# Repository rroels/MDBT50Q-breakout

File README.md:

# Raytac MDBT50Q (nRF52840) Breakout Board

> [!WARNING]
> The information and material (code, designs, files, ...) are provided "AS IS". We make no representation or warranty of any kind, express or implied, regarding the accuracy, adequacy, validity, reliability, availability, or completeness of any information or material. Use this at your own risk.

## Introduction

This is a breakout board for the Raytac MDBT50Q, which is small module based on the Nordic nRF52840 microcontroller.

[https://www.raytac.com/product/ins.php?index_id=24](https://www.raytac.com/product/ins.php?index_id=24)

This breakout board works with all three variants, since the only difference is their antenna:

* MDBT50Q-1MV2
* MDBT50Q-U1MV2
* MDBT50Q-P1MV2

Note that these modules are sometimes sold by other vendors, who put their own branding on the module:

* [https://www.adafruit.com/product/4078](https://www.adafruit.com/product/4078)
* [https://www.seeedstudio.com/MDBT50Q-1M-nRF52840-Based-BLE-Module-p-3147.html](https://www.seeedstudio.com/MDBT50Q-1M-nRF52840-Based-BLE-Module-p-3147.html)

This breakout board adds some power management and exposes most of the pins:

> [!WARNING]
> GPIO pins marked as "SLOW IO" are not slow per se. However, Nordic does not recommend using them for high frequency signals (e.g. SPI or I2C), as they may cause, or be subject to, interference (they are closest to the radio of the nRF52840).

## Change Log

* v1.0
  * Initial design 

## Design Considerations

* on-board 5V to 3.3V converter
* external 32.768K crystal (optional for the MDBT50Q module)
* ESD diode 
* reset button
* 1 LED 

## Schematics 

> [!WARNING]
> GPIO pins marked as "SLOW IO" are not slow per se. However, Nordic does not recommend using them for high frequency signals (e.g. SPI or I2C), as they may cause, or be subject to, interference (they are closest to the radio of the nRF52840).

## How to Obtain the Physical PCB

The Gerber file is in this repository (`gerber/MDBT50Q-breakout.zip`). Simply upload this file a PCB manufacturer of your choice (JLPCB, PCBWay, ...), and you they will make it for you for as low as \$5 for 5 pieces (with the cheapest shipping option, which can take a few weeks).

For JLCPCB, select the order number option where they will replace "JLCJLCJLCJLC" on the board with the actual order number.

> [!WARNING]
> Note that will still have to solder the components onto the PCB yourself!

## How to Edit Design

Everything you need to edit this design in KiCad 8 is included in the repository.

However, this project uses symbols, footprints and 3D models from [Component Search Engine](https://componentsearchengine.com/). Their license allows us to do pretty much whatever we want with them, except redistributing them. For this reason I can't include them in this repository.

If you would like to edit the design yourself, you will need to download the following component libraries from [https://componentsearchengine.com/](https://componentsearchengine.com/) (it's free!):

* [https://componentsearchengine.com/part-view/TS-1187A-C-D-B/XKB%20Connectivity](https://componentsearchengine.com/part-view/TS-1187A-C-D-B/XKB%20Connectivity)

You also need these from SnapEDA:

* [https://www.snapeda.com/parts/21296912/TE%20Connectivity/view-part/?ref=te_in&t=USB4105-GF-A&con_ref=None](https://www.snapeda.com/parts/21296912/TE%20Connectivity/view-part/?ref=te_in&t=USB4105-GF-A&con_ref=None)

From the downloaded zip files, move the content of the `KiCad` and `3D` subfolders into the project structure, so that the end-result looks like this:

The KiCad project is configured to look for these files in these locations, using relative paths, so no changes to the project itself are required.

## Future Work

* Improve routing
	* use more than 2 layer PCBs
* Add another push button for better compatibility with the Adafruit nRF52 bootloader	

## Sources

* [https://www.raytac.com/product/ins.php?index_id=24](https://www.raytac.com/product/ins.php?index_id=24)

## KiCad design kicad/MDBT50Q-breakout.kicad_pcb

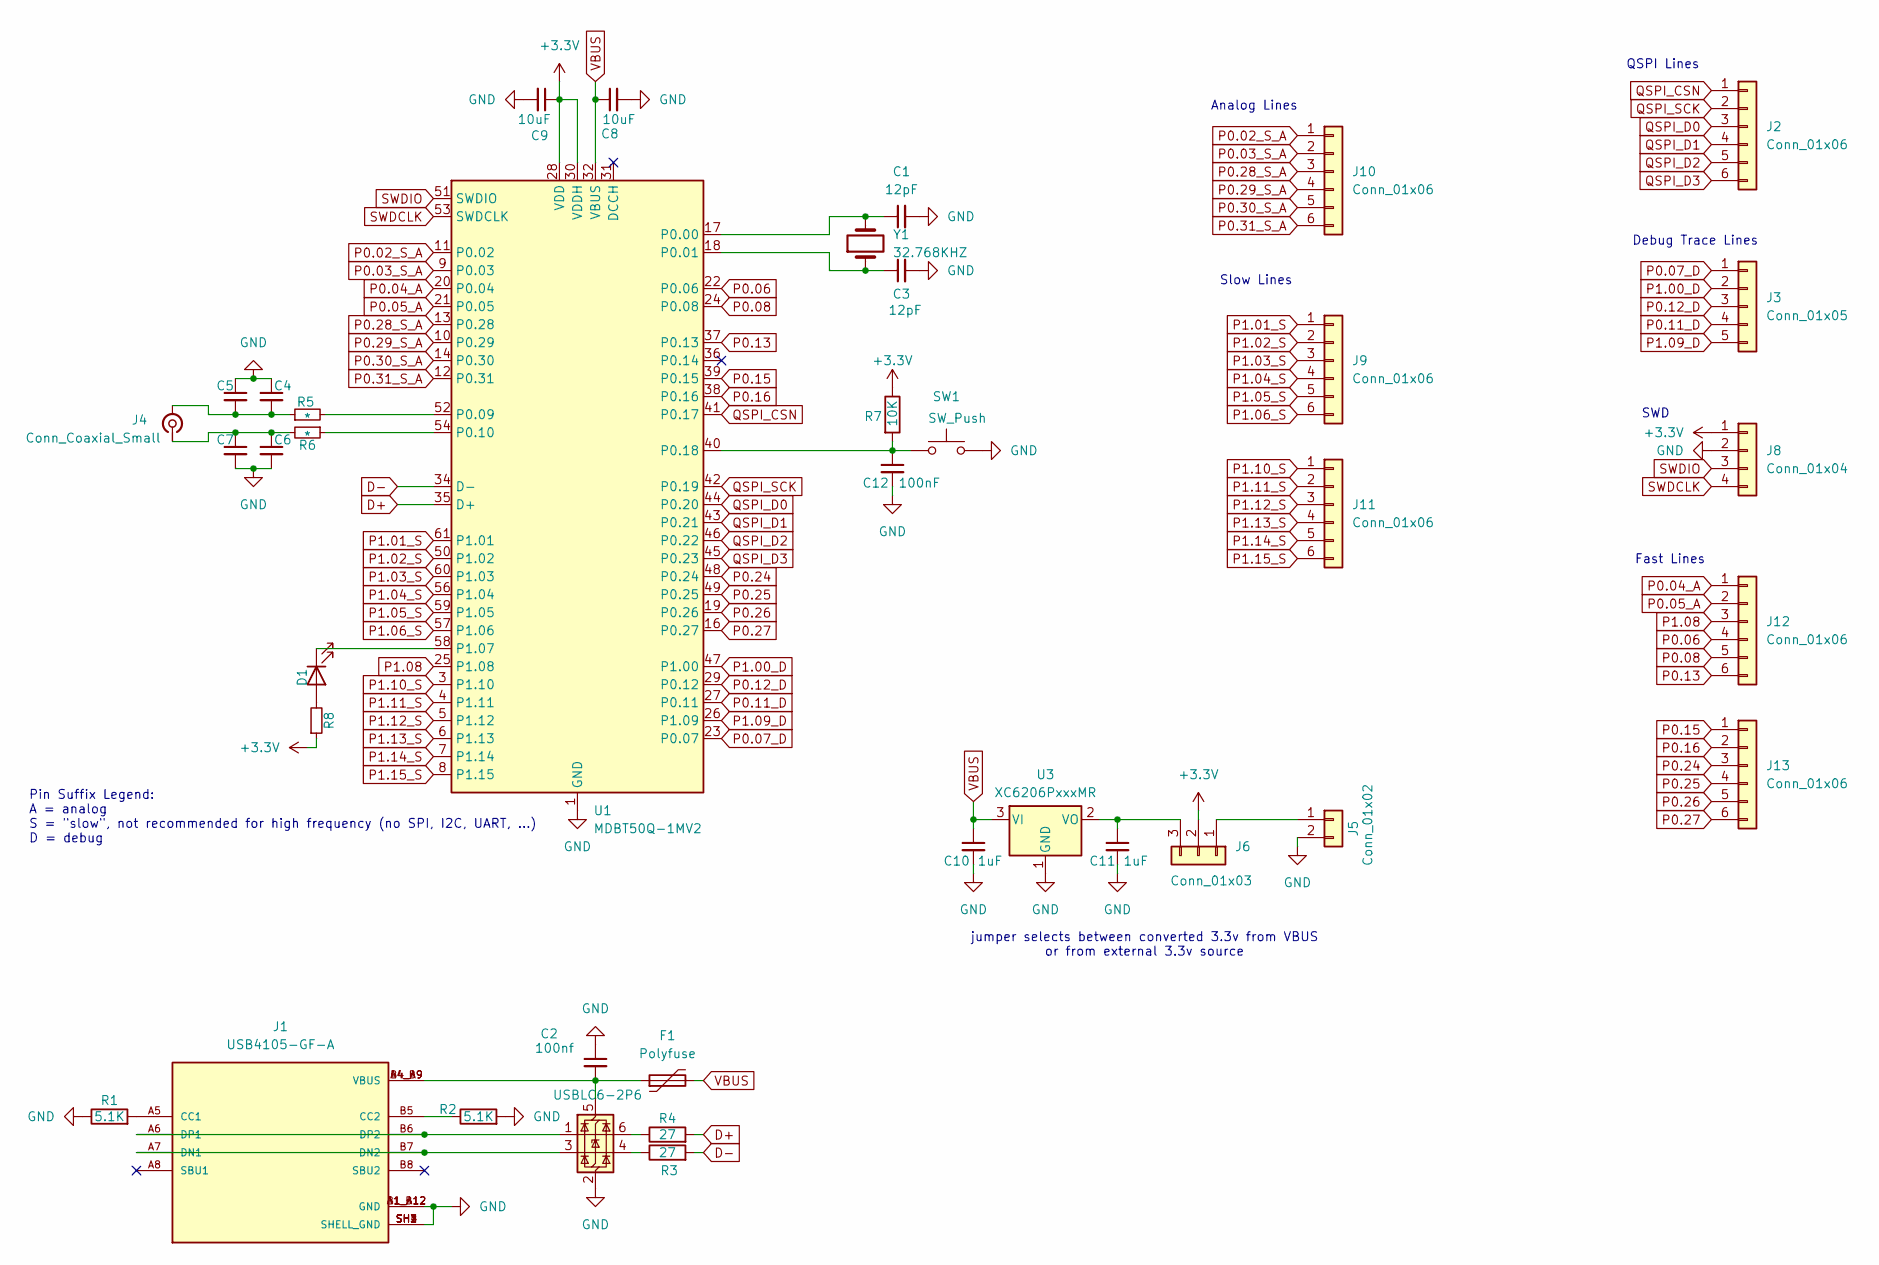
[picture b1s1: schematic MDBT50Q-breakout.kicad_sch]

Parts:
C1, C3: 12pF; C_0603_1608Metric_Pad1.08x0.95mm_HandSolder
C2: 100nf; C_0603_1608Metric_Pad1.08x0.95mm_HandSolder
C4, C5, C6, C7: C_Small; C_0603_1608Metric_Pad1.08x0.95mm_HandSolder
C8, C9: 10uF; C_0603_1608Metric_Pad1.08x0.95mm_HandSolder
C10, C11: 1uF; C_0603_1608Metric_Pad1.08x0.95mm_HandSolder
C12: 100nF; C_0603_1608Metric_Pad1.08x0.95mm_HandSolder
D1: LED; LED_0603_1608Metric_Pad1.05x0.95mm_HandSolder
F1: Polyfuse; Fuse_1206_3216Metric_Pad1.42x1.75mm_HandSolder
J1: USB4105-GF-A; GCT_USB4105-GF-A; PARTREV B4
J2, J9, J10, J11, J12, J13: Conn_01x06; PinHeader_1x06_P2.54mm_Vertical
J3: Conn_01x05; PinHeader_1x05_P2.54mm_Vertical
J4: Conn_Coaxial_Small; U.FL_Hirose_U.FL-R-SMT-1_Vertical
J5: Conn_01x02; PinHeader_1x02_P2.54mm_Vertical
J6: Conn_01x03; PinHeader_1x03_P2.54mm_Vertical
J8: Conn_01x04; PinHeader_1x04_P2.54mm_Vertical
R1, R2: 5.1K; R_0603_1608Metric_Pad0.98x0.95mm_HandSolder
R3, R4: 27; R_0603_1608Metric_Pad0.98x0.95mm_HandSolder
R5, R6: *; R_0603_1608Metric_Pad0.98x0.95mm_HandSolder
R7: 10K; R_0603_1608Metric_Pad0.98x0.95mm_HandSolder
R8: R_Small; R_0603_1608Metric_Pad0.98x0.95mm_HandSolder
SW1: SW_Push; SW_Push_1P1T_XKB_TS-1187A
U1: MDBT50Q-1MV2; Raytac_MDBT50Q
U2: USBLC6-2P6; SOT-666
U3: XC6206PxxxMR; SOT-23-3
Y1: 32.768KHZ; Crystal_SMD_3215-2Pin_3.2x1.5mm

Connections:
+3.3V: C9.1, J6.2, J8.1, R7.1, R8.1, U1.28 (VDD), U1.30 (VDDH)
D+: R4.2, U1.35 (D+)
D-: R3.2, U1.34 (D-)
GND: C1.2, C2.1, C3.2, C4.1, C5.1, C6.2, C7.2, C8.2, C9.2, C10.2, C11.2, C12.2, J1.A1_B12 (GND), J1.B1_A12 (GND), J1.SH1 (SHELL_GND), J1.SH2 (SHELL_GND), J1.SH3 (SHELL_GND), J1.SH4 (SHELL_GND), J5.2, J8.2, R1.1, R2.2, SW1.2, U1.1 (GND), U1.2 (GND), U1.15 (GND), U1.33 (GND), U1.55 (GND), U2.2 (GND), U3.1 (GND)
unnamed: D1.2 (A), R8.2
unnamed: D1.1 (K), U1.58 (P1.07)
unnamed: J1.A5 (CC1), R1.2
unnamed: J1.B5 (CC2), R2.1
unnamed: J1.A7 (DN1), J1.B7 (DN2), U2.3 (I/O2)
unnamed: J1.A6 (DP1), J1.B6 (DP2), U2.1 (I/O1)
unnamed: C4.2, C5.2, J4.2 (Ext), R5.1
unnamed: C6.1, C7.1, J4.1 (In), R6.2
unnamed: J5.1, J6.1
unnamed: C11.1, J6.3, U3.2 (VO)
unnamed: R3.1, U2.4 (I/O2)
unnamed: R4.1, U2.6 (I/O1)
unnamed: C1.1, U1.17 (P0.00), Y1.2
unnamed: C3.1, U1.18 (P0.01), Y1.1
unnamed: R5.2, U1.52 (P0.09)
unnamed: R6.1, U1.54 (P0.10)
unnamed: C12.1, R7.2, SW1.1, U1.40 (P0.18)
unnamed: C2.2, F1.1, J1.A4_B9 (VBUS), J1.B4_A9 (VBUS), U2.5 (VBUS)
P0.02_S_A: J10.1, U1.11 (P0.02)
P0.03_S_A: J10.2, U1.9 (P0.03)
P0.04_A: J12.1, U1.20 (P0.04)
P0.05_A: J12.2, U1.21 (P0.05)
P0.06: J12.4, U1.22 (P0.06)
P0.07_D: J3.1, U1.23 (P0.07)
P0.08: J12.5, U1.24 (P0.08)
P0.11_D: J3.4, U1.27 (P0.11)
P0.12_D: J3.3, U1.29 (P0.12)
P0.13: J12.6, U1.37 (P0.13)
P0.15: J13.1, U1.39 (P0.15)
P0.16: J13.2, U1.38 (P0.16)
P0.24: J13.3, U1.48 (P0.24)
P0.25: J13.4, U1.49 (P0.25)
P0.26: J13.5, U1.19 (P0.26)
P0.27: J13.6, U1.16 (P0.27)
P0.28_S_A: J10.3, U1.13 (P0.28)
P0.29_S_A: J10.4, U1.10 (P0.29)
P0.30_S_A: J10.5, U1.14 (P0.30)
P0.31_S_A: J10.6, U1.12 (P0.31)
P1.00_D: J3.2, U1.47 (P1.00)
P1.01_S: J9.1, U1.61 (P1.01)
P1.02_S: J9.2, U1.50 (P1.02)
P1.03_S: J9.3, U1.60 (P1.03)
P1.04_S: J9.4, U1.56 (P1.04)
P1.05_S: J9.5, U1.59 (P1.05)
P1.06_S: J9.6, U1.57 (P1.06)
P1.08: J12.3, U1.25 (P1.08)
P1.09_D: J3.5, U1.26 (P1.09)
P1.10_S: J11.1, U1.3 (P1.10)
P1.11_S: J11.2, U1.4 (P1.11)
P1.12_S: J11.3, U1.5 (P1.12)
P1.13_S: J11.4, U1.6 (P1.13)
P1.14_S: J11.5, U1.7 (P1.14)
P1.15_S: J11.6, U1.8 (P1.15)
QSPI_CSN: J2.1, U1.41 (P0.17)
QSPI_D0: J2.3, U1.44 (P0.20)
QSPI_D1: J2.4, U1.43 (P0.21)
QSPI_D2: J2.5, U1.46 (P0.22)
QSPI_D3: J2.6, U1.45 (P0.23)
QSPI_SCK: J2.2, U1.42 (P0.19)
SWDCLK: J8.4, U1.53 (SWDCLK)
SWDIO: J8.3, U1.51 (SWDIO)
VBUS: C8.1, C10.1, F1.2, U1.32 (VBUS), U3.3 (VI)

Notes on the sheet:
Slow Lines
SWD
jumper selects between converted 3.3v from VBUS or from external 3.3v source
Debug Trace Lines
Analog Lines
QSPI Lines
Fast Lines
Pin Suffix Legend: A = analog S = "slow", not recommended for high frequency (no SPI, I2C, UART, ...) D = debug

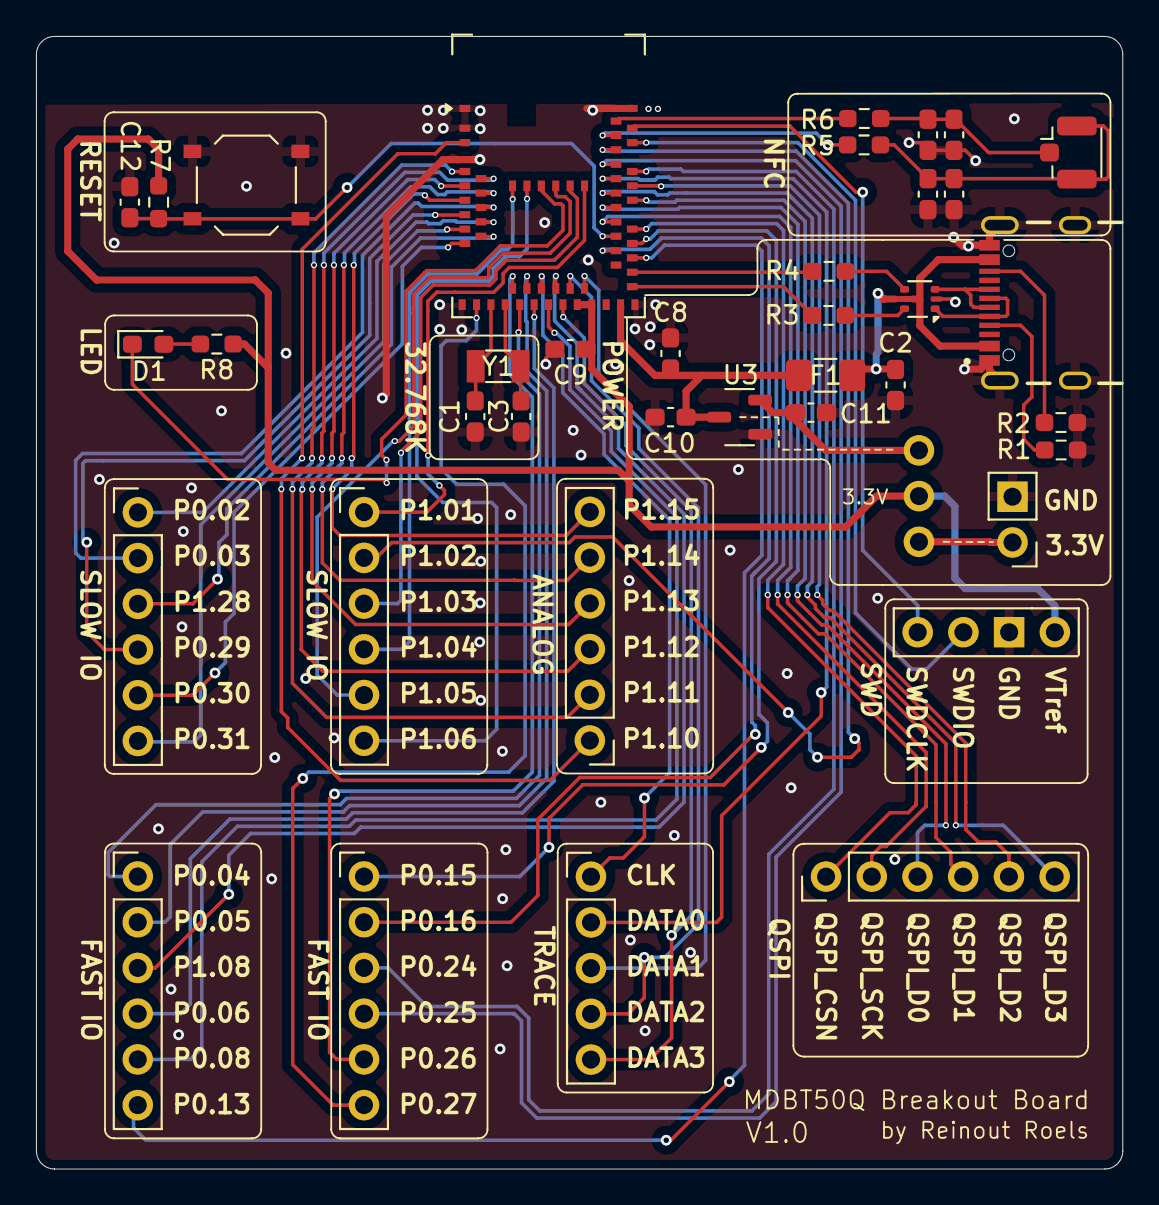
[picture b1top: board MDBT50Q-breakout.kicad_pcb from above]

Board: 2 copper layers, 60.4 x 62.9 mm, 39 parts (0 on the bottom side), 66 nets.
